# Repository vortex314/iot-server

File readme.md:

# IOT-Server
Start a mini PC that can act as a home centralized IOT-server with different middleware functionalities
Based on Docker containers 
## Features
- MQTT Mosquitto
- Portainer 
- some EspHome scripts for devices
- web-socket server to Redis
- Redis server
- UDP server to Redis
- Zenoh Router ( the ultimate endgame ... hopefully )
- SMA reader , forward to MQTT
- Home Assistant
## Zenoh Router
- support multicast discovery 
- support udp/tcp
- support multicast peers with predefined buffer size
- exposed outside via HTTP / TCP
# Deployment
- Install Docker 
```
get-docker.sh
```
- Deploy portainer
```
./portainer.sh
./redis.sh
./sma_reader.sh
./mqtt.sh
```

# Zenoh mqtt bridge
https://github.com/eclipse-zenoh/zenoh-plugin-mqtt

docker run --init -p 1883:1883 eclipse/zenoh-bridge-mqtt
https://github.com/eclipse-zenoh/zenoh-plugin-mqtt/blob/main/DEFAULT_CONFIG.json5

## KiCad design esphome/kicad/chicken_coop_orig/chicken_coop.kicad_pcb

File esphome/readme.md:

# IOT SERVER 
- settings and scripts for my home assistant setup
- docker containers for 
-- redis
-- mqtt
-- portainer
-- home assistant
-- SMA data colection via SBFspot line command
- esphome files for :
-- camera
-- bluetooth scanner

## MQTT structure of home-assistant

[MQTT structure](https://www.home-assistant.io/integrations/mqtt/#broker-configuration)
https://www.home-assistant.io/integrations/binary_sensor.mqtt/
### Discovery 
homeassistant/<component>/<optional node_id>/<object_id>/config
example 
homeassistant/sensor/SMA_2100466612/UDC2/config
```json
{
  "name": "SMA_2100466612_UDC2",
  "device_class": "voltage",
  "state_topic": "SMA_2100466612",
  "state_class": "measurement",
  "value_template": "{{ value_json.UDC2}}",
  "unique_id": "SMA_2100466612/UDC2",
  "unit_of_measurement": "V"
}
```
### Birth message
homeasssitant/status 

# ESP8266 with L293D motor driver
Hackaday article : https://hackaday.io/project/8856-incubator-controller/log/29291-node-mcu-motor-shield

# ESP32 CAM board
- tricky boot connect 

![drv8871](./doc/drv8871.png
)

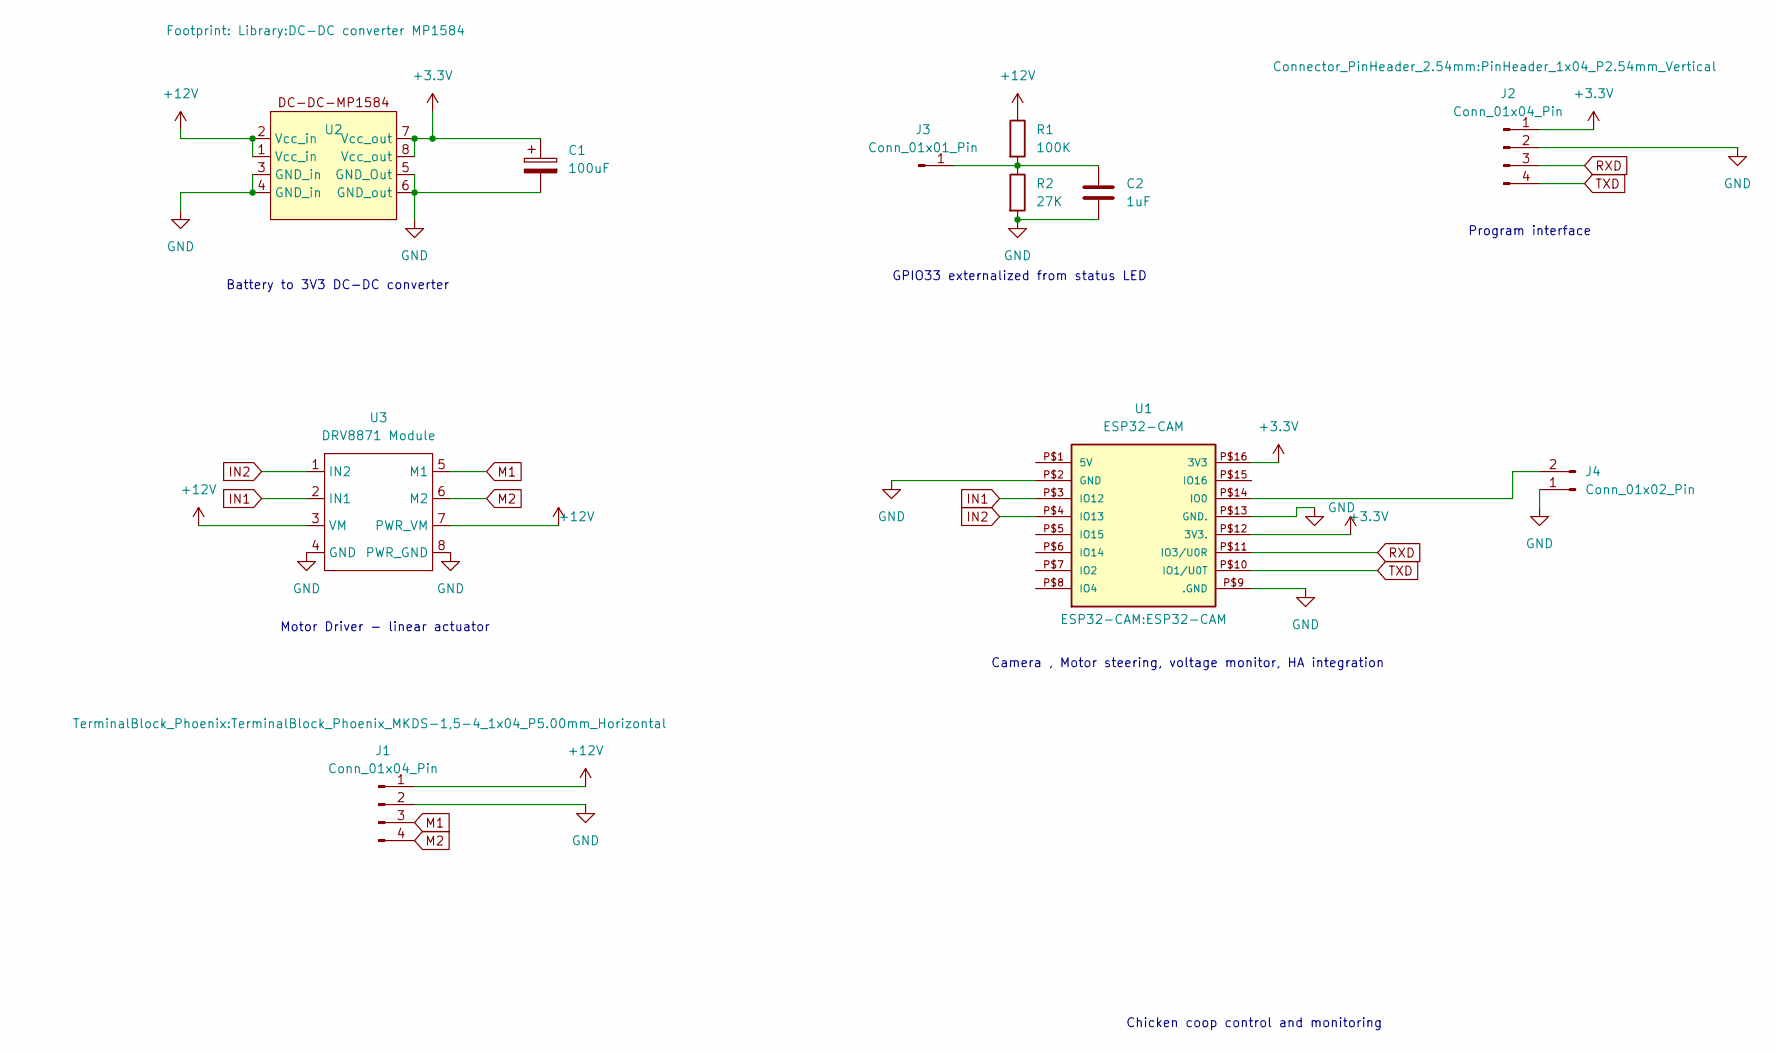
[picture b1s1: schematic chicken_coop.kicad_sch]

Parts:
C1: 100uF; CP_Radial_D10.0mm_P5.00mm
C2: 1uF; C_Disc_D8.0mm_W2.5mm_P5.00mm
J1: Conn_01x04_Pin; TerminalBlock_Phoenix_MKDS-1,5-4_1x04_P5.00mm_Horizontal
J2: Conn_01x04_Pin; PinHeader_1x04_P2.54mm_Vertical
J3: Conn_01x01_Pin; PinHeader_1x01_P2.54mm_Vertical
J4: Conn_01x02_Pin; PinHeader_1x02_P2.54mm_Vertical
R1: 100K; R_Axial_DIN0207_L6.3mm_D2.5mm_P7.62mm_Horizontal
R2: 27K; R_Axial_DIN0207_L6.3mm_D2.5mm_P7.62mm_Horizontal
U1: ESP32-CAM
U2: DC-DC converter MP1584
U3: DRV8871 Module; DRV8871 MODULE

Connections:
+3.3V: C1.1, J2.1, U1.P$12 (3V3.), U1.P$16 (3V3), U2.7 (Vcc_out), U2.8 (Vcc_out)
+12V: J1.1, R1.1, U2.1 (Vcc_in), U2.2 (Vcc_in), U3.3 (VM), U3.7 (PWR_VM)
GND: C1.2, C2.2, J1.2, J2.2, J4.1, R2.2, U1.P$2 (GND), U1.P$9 (.GND), U1.P$13 (GND.), U2.3 (GND_in), U2.4 (GND_in), U2.5 (GND_Out), U2.6 (GND_out), U3.4 (GND), U3.8 (PWR_GND)
IN1: U1.P$3 (IO12), U3.2 (IN1)
IN2: U1.P$4 (IO13), U3.1 (IN2)
M1: J1.3, U3.5 (M1)
M2: J1.4, U3.6 (M2)
unnamed: C2.1, J3.1, R1.2, R2.1
unnamed: J4.2, U1.P$14 (IO0)
RXD: J2.3, U1.P$11 (IO3/U0R)
TXD: J2.4, U1.P$10 (IO1/U0T)

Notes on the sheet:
Program interface
Battery to 3V3 DC-DC converter
Motor Driver - linear actuator
Chicken coop control and monitoring
GPIO33 externalized from status LED
Camera , Motor steering, voltage monitor, HA integration

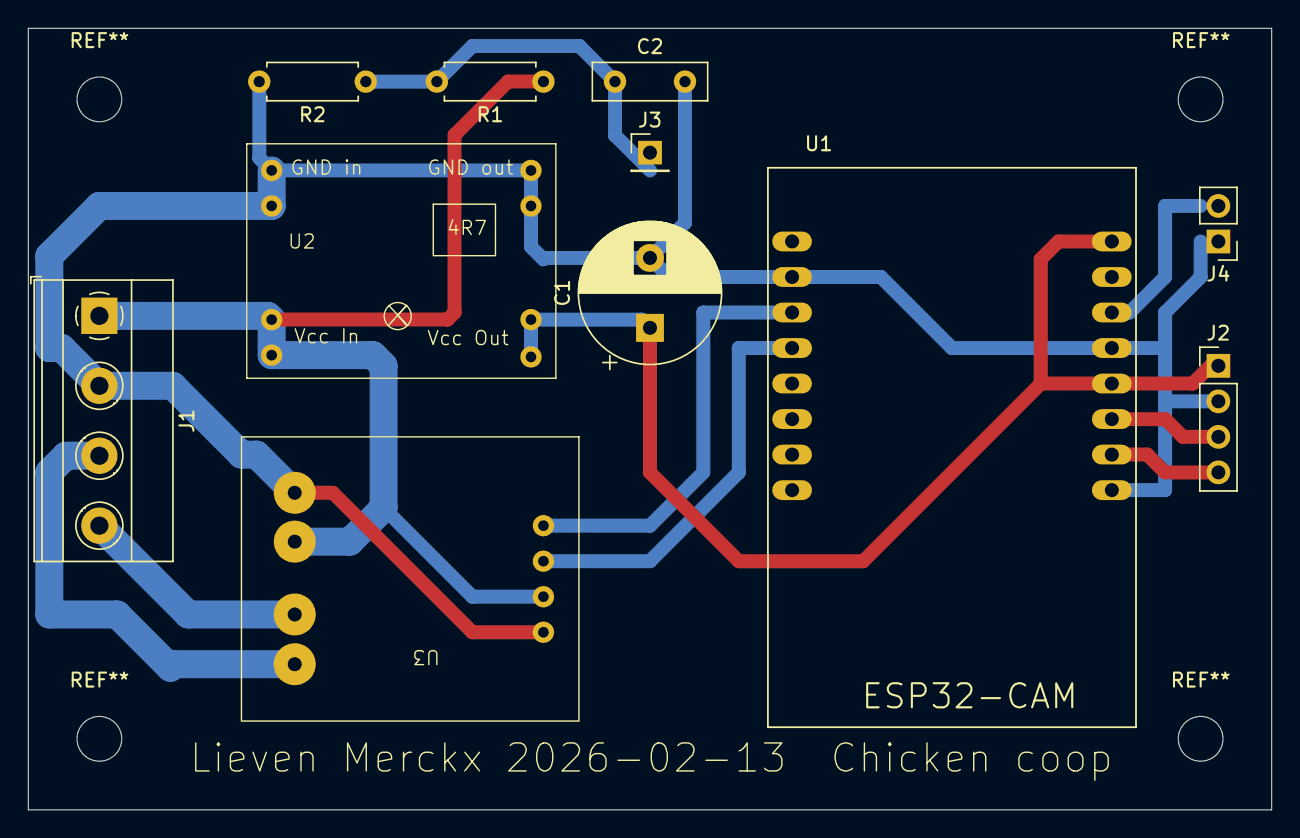
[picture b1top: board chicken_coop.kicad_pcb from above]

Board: 2 copper layers, 88.9 x 55.9 mm, 11 parts (0 on the bottom side), 11 nets.

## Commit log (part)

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2023-07-22 start
2023-07-22 added udp2redis server
2023-07-22 udp2redis proof
2023-07-26 added sma_reader
2024-01-15 added ws2
2024-04-28 added elastic
2024-05-03 esphome
2024-05-05 sync
2024-06-09 add redisBrain for treeSHaker
2025-02-13 updating for zenoh replacing redis
2025-02-14 aadded zenoh
2025-02-16 working zenoh config, but unclear why
2025-02-17 debug logging zenoh
2025-02-17 debug config
2025-02-18 aaccept only IP4
2025-03-03 P1 in progress
2025-03-03 added P1 energy meter
2025-03-09 P1 reader ok
2025-03-11 HA update
2025-03-11 sync esp p1
2025-04-05 dsmr reader
2025-04-10 added peak tariff entries
2025-06-01 added tree shakers
2026-03-07 sync kicad
2026-03-07 sync footprint from picture
2026-03-19 sync , 1k led res
2026-03-22 adc ok, cam image schema updated
2026-05-29 updated shakers
2026-05-31 evcc added
2026-06-03 sync evcc
